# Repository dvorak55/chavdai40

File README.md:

# Chavdai40% Socketをご購入の方はこちら↓
https://github.com/dvorak55/chavdai40socket

# 2020年、2023年発売のChavdai40%をご購入の方で、以前のサポートページをご覧になりたい方はこちら↓
https://github.com/dvorak55/chavdai40/tree/master/2023

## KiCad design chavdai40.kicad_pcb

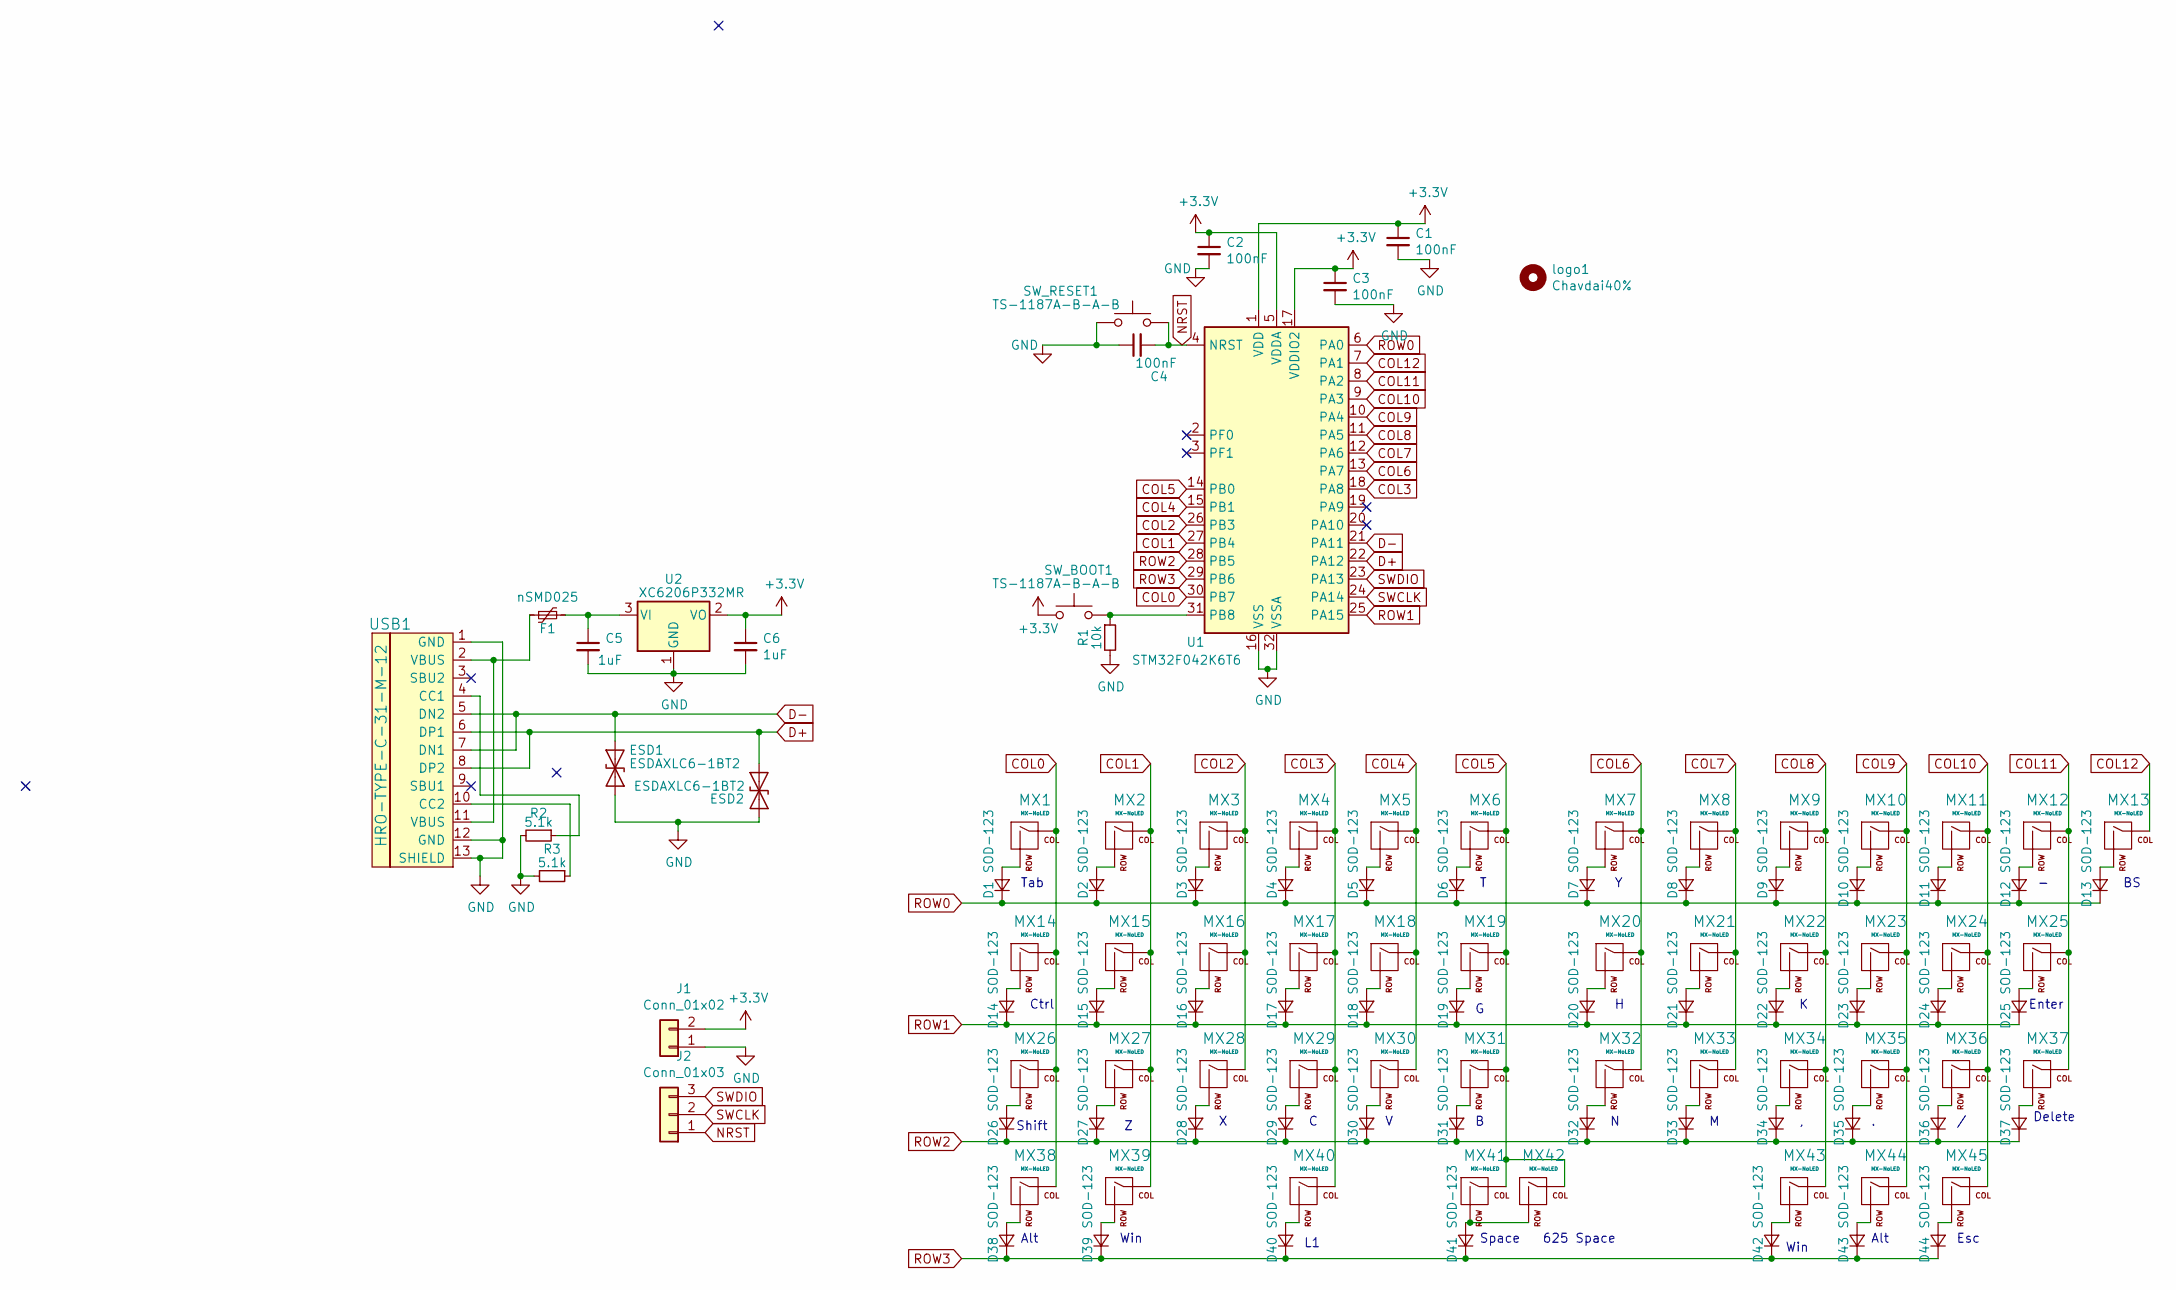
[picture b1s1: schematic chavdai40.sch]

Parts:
C1, C2, C3, C4: 100nF; C_0402_1005Metric
C5, C6: 1uF; C_0603_1608Metric
D1, D2, D3, D4, D5, D6, D7, D8, D9, D10, D11, D12, D13, D14, D15, D16, D17, D18, D19, D20, D21, D22, D23, D24, D25, D26, D27, D28, D29, D30, D31, D32, D33, D34, D35, D36, D37, D38, D39, D40, D41, D42, D43, D44: SOD-123; D_SOD-123
ESD1, ESD2: ESDAXLC6-1BT2; D_0402_1005Metric
F1: nSMD025; Fuse_1206_3216Metric
J1: Conn_01x02; PinHeader_1x02_P2.54mm_Vertical
J2: Conn_01x03; PinHeader_1x03_P2.54mm_Vertical
MX1, MX13: MX-NoLED; MXOnly-1.5U-NoLED
MX2, MX3, MX4, MX5, MX6, MX7, MX8, MX9, MX10, MX11, MX12, MX15, MX16, MX17, MX18, MX19, MX20, MX21, MX22, MX23, MX24, MX27, MX28, MX29, MX30, MX31, MX32, MX33, MX34, MX35: MX-NoLED; MXOnly-1U-NoLED
MX14: MX-NoLED; MXOnly-1.75U-NoLED
MX25: MX-NoLED; MXOnly-2.25U-NoLED
MX26, MX40: MX-NoLED; MXOnly-2.25U-ReversedStabilizers-NoLED
MX36, MX37, MX38, MX39, MX43, MX44, MX45: MX-NoLED; MXOnly-1.25U-NoLED
MX41: MX-NoLED; MXOnly-2.75U-ReversedStabilizers-NoLED
MX42: MX-NoLED; MXOnly-6.25U-ReversedStabilizers-NoLED
R1: 10k; R_0603_1608Metric
R2, R3: 5.1k; R_0603_1608Metric
SW_BOOT1: TS-1187A-B-A-B; SKQGADE010
SW_RESET1: TS-1187A-B-A-B; SKQGADE010
U1: STM32F042K6T6; LQFP-32_7x7mm_P0.8mm
U2: XC6206P332MR; TSOT-23
USB1: HRO-TYPE-C-31-M-12; HRO-TYPE-C-31-M-12-HandSoldering
logo1: Chavdai40%; logo2-small

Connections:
+3V3: C1.1, C2.1, C3.1, C6.1, J1.2, SW_BOOT1.1, U1.1 (VDD), U1.5 (VDDA), U1.17 (VDDIO2), U2.2 (VO)
COL0: MX1.1 (COL), MX14.1 (COL), MX26.1 (COL), MX38.1 (COL), U1.30 (PB7)
COL1: MX2.1 (COL), MX15.1 (COL), MX27.1 (COL), MX39.1 (COL), U1.27 (PB4)
COL2: MX3.1 (COL), MX16.1 (COL), MX28.1 (COL), U1.26 (PB3)
COL3: MX4.1 (COL), MX17.1 (COL), MX29.1 (COL), MX40.1 (COL), U1.18 (PA8)
COL4: MX5.1 (COL), MX18.1 (COL), MX30.1 (COL), U1.15 (PB1)
COL5: MX6.1 (COL), MX19.1 (COL), MX31.1 (COL), MX41.1 (COL), MX42.1 (COL), U1.14 (PB0)
COL6: MX7.1 (COL), MX20.1 (COL), MX32.1 (COL), U1.13 (PA7)
COL7: MX8.1 (COL), MX21.1 (COL), MX33.1 (COL), U1.12 (PA6)
COL8: MX9.1 (COL), MX22.1 (COL), MX34.1 (COL), MX43.1 (COL), U1.11 (PA5)
COL9: MX10.1 (COL), MX23.1 (COL), MX35.1 (COL), MX44.1 (COL), U1.10 (PA4)
COL10: MX11.1 (COL), MX24.1 (COL), MX36.1 (COL), MX45.1 (COL), U1.9 (PA3)
COL11: MX12.1 (COL), MX25.1 (COL), MX37.1 (COL), U1.8 (PA2)
COL12: MX13.1 (COL), U1.7 (PA1)
D+: ESD2.2 (A2), U1.22 (PA12), USB1.6 (DP1), USB1.8 (DP2)
D-: ESD1.1 (A1), U1.21 (PA11), USB1.5 (DN2), USB1.7 (DN1)
GND: C1.2, C2.2, C3.2, C4.1, C5.2, C6.2, ESD1.2 (A2), ESD2.1 (A1), J1.1, R1.2, R2.2, R3.2, SW_RESET1.1, U1.16 (VSS), U1.32 (VSSA), U2.1 (GND), USB1.1 (GND), USB1.12 (GND), USB1.13 (SHIELD)
NRST: C4.2, J2.1, SW_RESET1.2, U1.4 (NRST)
unnamed: C5.1, F1.1, U2.3 (VI)
unnamed: D1.2 (A), MX1.2 (ROW)
unnamed: D2.2 (A), MX2.2 (ROW)
unnamed: D3.2 (A), MX3.2 (ROW)
unnamed: D4.2 (A), MX4.2 (ROW)
unnamed: D5.2 (A), MX5.2 (ROW)
unnamed: D6.2 (A), MX6.2 (ROW)
unnamed: D7.2 (A), MX7.2 (ROW)
unnamed: D8.2 (A), MX8.2 (ROW)
unnamed: D9.2 (A), MX9.2 (ROW)
unnamed: D10.2 (A), MX10.2 (ROW)
unnamed: D11.2 (A), MX11.2 (ROW)
unnamed: D12.2 (A), MX12.2 (ROW)
unnamed: D13.2 (A), MX13.2 (ROW)
unnamed: D14.2 (A), MX14.2 (ROW)
unnamed: D15.2 (A), MX15.2 (ROW)
unnamed: D16.2 (A), MX16.2 (ROW)
unnamed: D17.2 (A), MX17.2 (ROW)
unnamed: D18.2 (A), MX18.2 (ROW)
unnamed: D19.2 (A), MX19.2 (ROW)
unnamed: D20.2 (A), MX20.2 (ROW)
unnamed: D21.2 (A), MX21.2 (ROW)
unnamed: D22.2 (A), MX22.2 (ROW)
unnamed: D23.2 (A), MX23.2 (ROW)
unnamed: D24.2 (A), MX24.2 (ROW)
unnamed: D25.2 (A), MX25.2 (ROW)
unnamed: D26.2 (A), MX26.2 (ROW)
unnamed: D27.2 (A), MX27.2 (ROW)
unnamed: D28.2 (A), MX28.2 (ROW)
unnamed: D29.2 (A), MX29.2 (ROW)
unnamed: D30.2 (A), MX30.2 (ROW)
unnamed: D31.2 (A), MX31.2 (ROW)
unnamed: D32.2 (A), MX32.2 (ROW)
unnamed: D33.2 (A), MX33.2 (ROW)
unnamed: D34.2 (A), MX34.2 (ROW)
unnamed: D35.2 (A), MX35.2 (ROW)
unnamed: D36.2 (A), MX36.2 (ROW)
unnamed: D37.2 (A), MX37.2 (ROW)
unnamed: D38.2 (A), MX38.2 (ROW)
unnamed: D39.2 (A), MX39.2 (ROW)
unnamed: D40.2 (A), MX40.2 (ROW)
unnamed: D41.2 (A), MX41.2 (ROW), MX42.2 (ROW)
unnamed: D42.2 (A), MX43.2 (ROW)
unnamed: D43.2 (A), MX44.2 (ROW)
unnamed: D44.2 (A), MX45.2 (ROW)
unnamed: F1.2, USB1.2 (VBUS), USB1.11 (VBUS)
unnamed: R1.1, SW_BOOT1.2, U1.31 (PB8)
unnamed: R2.1, USB1.4 (CC1)
unnamed: R3.1, USB1.10 (CC2)
ROW0: D1.1 (K), D2.1 (K), D3.1 (K), D4.1 (K), D5.1 (K), D6.1 (K), D7.1 (K), D8.1 (K), D9.1 (K), D10.1 (K), D11.1 (K), D12.1 (K), D13.1 (K), U1.6 (PA0)
ROW1: D14.1 (K), D15.1 (K), D16.1 (K), D17.1 (K), D18.1 (K), D19.1 (K), D20.1 (K), D21.1 (K), D22.1 (K), D23.1 (K), D24.1 (K), D25.1 (K), U1.25 (PA15)
ROW2: D26.1 (K), D27.1 (K), D28.1 (K), D29.1 (K), D30.1 (K), D31.1 (K), D32.1 (K), D33.1 (K), D34.1 (K), D35.1 (K), D36.1 (K), D37.1 (K), U1.28 (PB5)
ROW3: D38.1 (K), D39.1 (K), D40.1 (K), D41.1 (K), D42.1 (K), D43.1 (K), D44.1 (K), U1.29 (PB6)
SWCLK: J2.2, U1.24 (PA14)
SWDIO: J2.3, U1.23 (PA13)

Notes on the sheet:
Esc
Alt
Win
Delete
Enter
Space
Ctrl
Shift
Tab
625 Space

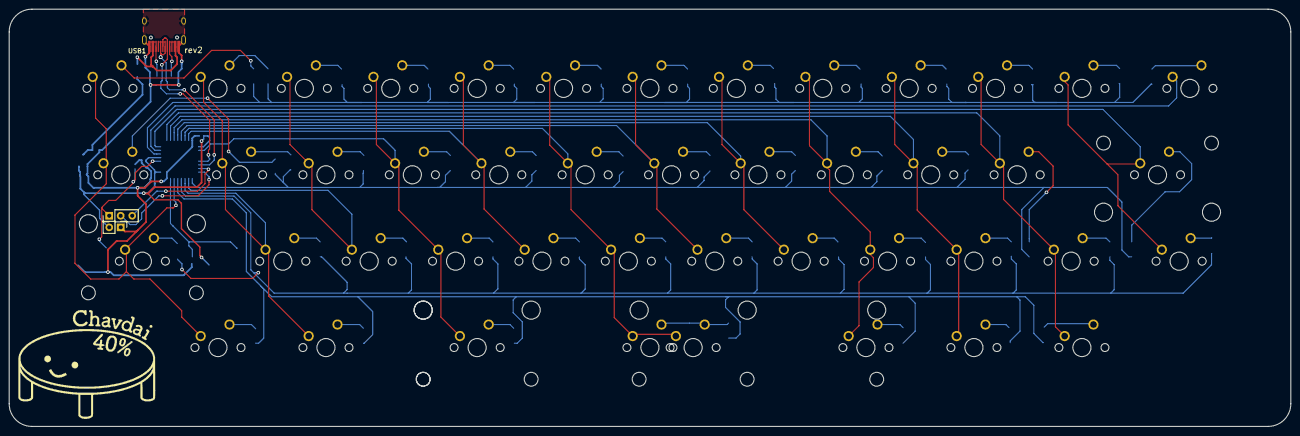
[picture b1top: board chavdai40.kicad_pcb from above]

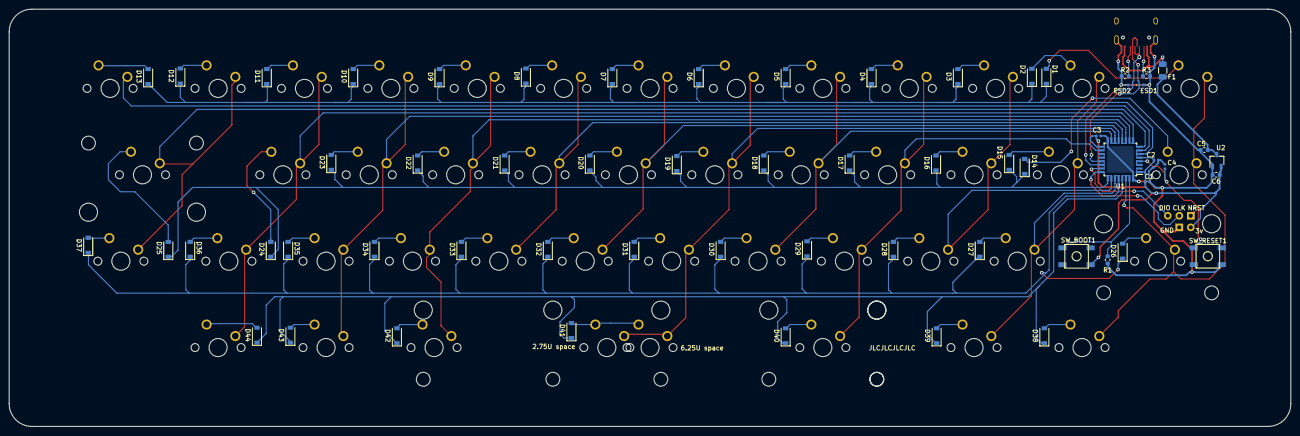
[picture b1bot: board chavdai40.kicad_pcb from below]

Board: 2 copper layers, 282.6 x 92.0 mm, 109 parts (60 on the bottom side), 73 nets.

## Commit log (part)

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2020-05-02 keylayout and keymap create
2020-05-02 kicad init
2020-05-02 Add submodules
2020-05-02 add footprint libraries
2020-05-03 Add submodule usb-c
2020-05-03 make a schematic
2020-05-04 usb 22ohm register remove; pas-con remove
2020-05-08 2020-05-09 PCB dekita
2020-05-17 tabun dekita
2020-06-03 some file to directory
2020-07-25 add keymap picture
2020-07-27 add impl picture
2020-07-27 add keylayout png files
2020-08-04 rename jpg for readme.md
2020-08-10 update readme.md picture
2020-08-16 update impliment procedure
2020-08-16 update readme picture
2020-09-01 update chavdai pcb design(rev2)
2020-09-13 add rev2 description
2020-09-13 update readme.md for rev2 description
2020-09-13 add firmware for rev2
2020-10-15 add link of how to write firmware on Linux
    thanks for @_Shallot_.
    add link of how to write firmware on Linux.
2023-07-24 Update README.md
    update for 2023.
2023-07-29 white pcb photo add
2023-07-29 Update README.md
    add white pcb photos
2023-12-12 test back panel kicad file added.
2023-12-18 Update README.md
    Vial porting.
2023-12-22 Update README.md
    add Vial firmware text
